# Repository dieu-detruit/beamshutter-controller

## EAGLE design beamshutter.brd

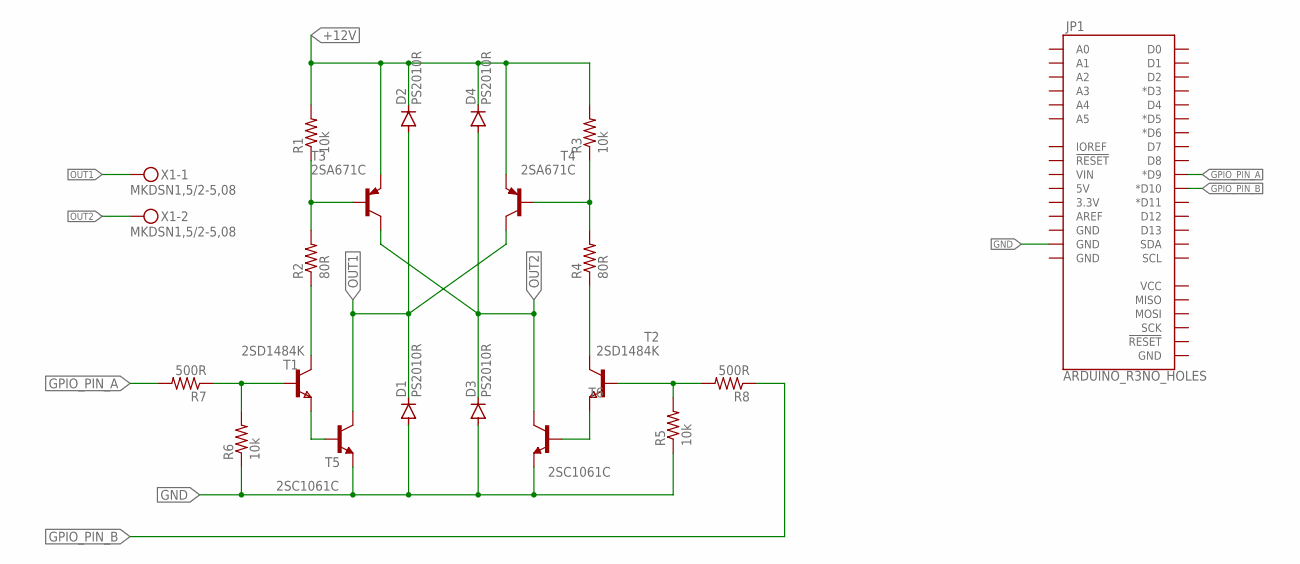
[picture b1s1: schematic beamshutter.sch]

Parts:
D1, D2, D3, D4: PS2010R; DO15-12
JP1: ARDUINO_R3NO_HOLES; ARDUINO_R3_NO_HOLES
R1, R3, R5, R6: 10k; 2012-R
R2, R4: 80R; 2012-R
R7, R8: 500R; 2012-R
T1, T2: 2SD1484K; SOT323
T3, T4: 2SA671C; TO220V
T5, T6: 2SC1061C; TO220V
X1: MKDSN1,5/2-5,08

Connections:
+12V: D2.C, D4.C, R1.2, R3.2, T3.3 (E), T4.3 (E)
GND: D1.A, D3.A, JP1.GND@3 (GND), R5.1, R6.1, T5.3 (E), T6.3 (E)
GPIO_PIN_A: JP1.D9 (*D9), R7.2
GPIO_PIN_B: JP1.D10 (*D10), R8.1
unnamed: R6.2, R7.1, T1.2 (B)
unnamed: R1.1, R2.2, T3.1 (B)
unnamed: R3.1, R4.2, T4.1 (B)
unnamed: R5.2, R8.2, T2.2 (B)
unnamed: T1.3 (E), T5.1 (B)
unnamed: T2.3 (E), T6.1 (B)
unnamed: R4.1, T2.1 (C)
unnamed: R2.1, T1.1 (C)
OUT1: D1.C, D2.A, T4.2 (C), T5.2 (C), X1.1
OUT2: D3.C, D4.A, T3.2 (C), T6.2 (C), X1.2

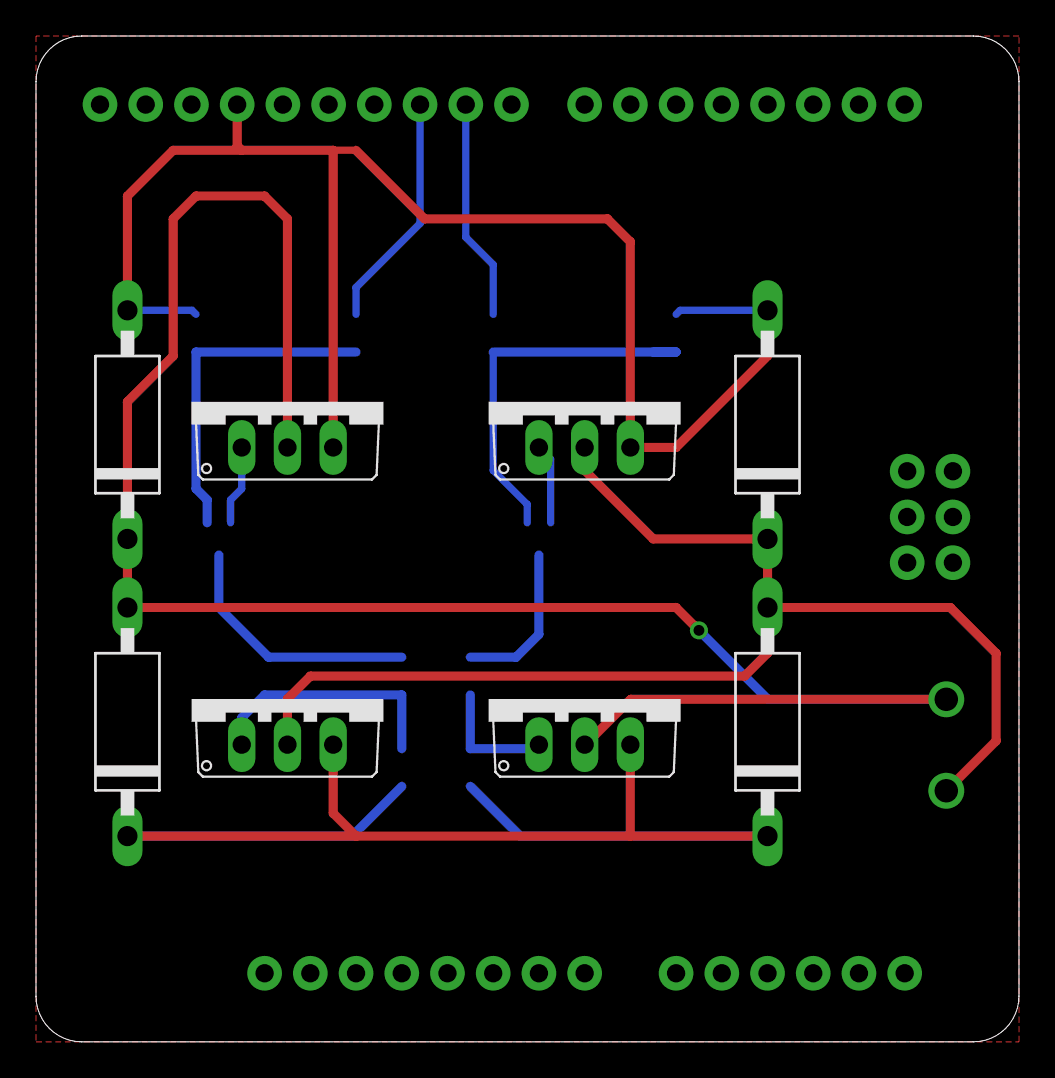
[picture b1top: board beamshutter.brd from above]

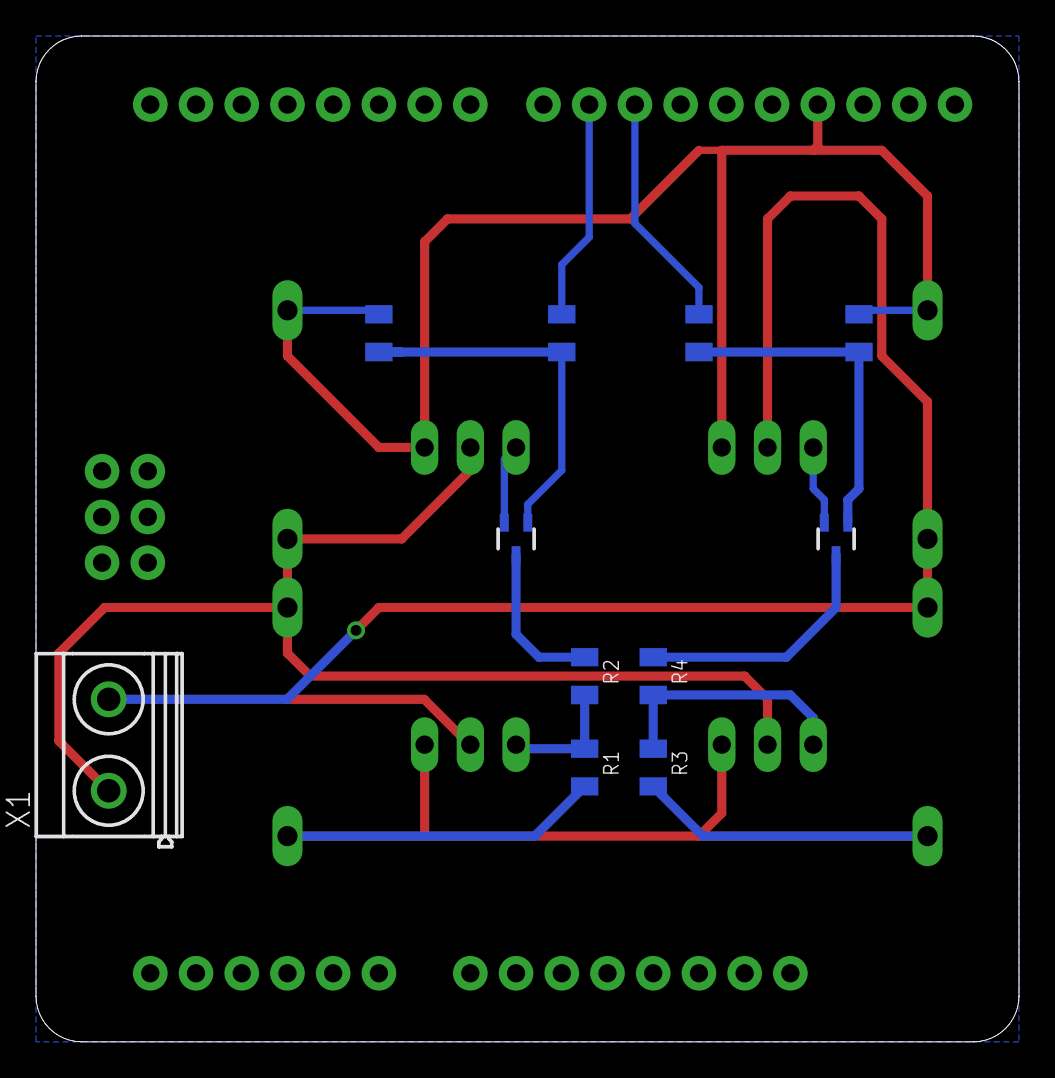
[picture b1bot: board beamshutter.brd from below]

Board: 2 copper layers, 54.6 x 55.9 mm, 20 parts (11 on the bottom side), 14 nets.

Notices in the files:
parts and their libraries:
SparkFun-Boards: Licensing: Creative Commons ShareAlike 4.0 International - https://creativecommons.org/licenses/by-sa/4.0
